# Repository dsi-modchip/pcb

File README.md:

# DSi modchip PCB and flex-cable

> [!IMPORTANT]
> ***This PCB is still a work-in-progress and has bugs.***

This repository contains the KiCAD design files for the DSi modchip and the
cable flex-PCB.

## Notes

Currently, you'll have to order and make these yourself. I don't think making
them widely available already is a good idea, there's still a few bugs left in
the design.

The issues with the modchip PCB itself are listed [here](/wifi-interposer/TODO-r2.2.).
Additionally, inserting a cable into the modchips USB socket too forcefully can
cause the modchip PCB to snap in half, which is bad.

I haven't actually gotten the flex-cable to work properly. There are problems
with either a too large parasitic capacitance on the glitch signal line, or bad
contacts between the flexPCB and the glitching MOSFET. I suggest deadbugging
the crowbar MOSFET instead, if that's something you're capable of.

## Ordering/fab instructions

The modchip is a 4-layer board that should be 0.8 mm thick. I've gotten it
fabbed successfully from both Aisler (at 1.6mm thickness) and JLCPCB.

The flex-cable consists of two layers, needs stiffner in certain places, and
has been fabbed from JLCPCB.

## Bill of Materials

### Modchip main components

These are all the components required for the core functionality of the modchip.

| Reference | Value       | Footprint | Qty | Farnell n° | LCSC n° | Mouser n° |
|:--------- |:----------- |:--------- | ---:| ----------:| -------:|:--------- |
| C3,C4     | 27pF C0G    | 0402      | 2   | 4539081    | C880615 | 603-CC402GRNPO9BN270 |
| C5,C6,C7,C10,C11,C12,C13,C14,C15,C16,C17 | 100nF | 0402 | 11 | 1758880 | C16772 | 791-0402B224K100CT |
| C8,C9     | 1uF         | 0402      | 2   | 3013332    | C12530  | 187-CL05A105KP5NNNC |
| J1        | Molex SlimStack 501920-5001 | | 1 | N/A    | N/A     | 538-501920-5001 |
| J5        | Molex 200528-0040 |     | 1   | 3500399    | N/A     | 538-200528-0040 |
| Q4        | Dual NPMOS  | SOT-363/SC-70-6|1|3828400    | C155499 | 621-DMC3400SDW-13 |
| R1,R2     | 10k         | 0402      | 2   | 2787800    | C25744  | 279-CRG0402J10K/10 |
| R5        | 47k         | 0402      | 2   | 4004532    | C25792  | 279-CRG0402J47K |
| R7,R8     | 1k          | 0402      | 2   | 4004531    | C11702  | 603-RC0402FR-131KL |
| SW1, SW2  | 1P1T button | 4.2x3.2mm | 2   | 3703693    | C2689510| 611-RKB2SJM250SMTRLF |
| U1        | RP2040      | QFN-56 P0.4 | 1 | 3766082    | C2040   | 358-SC09147 |
| U2,U4     | W25Q16JVUXIQ | DFN-8 P0.5mm |2| N/A        | C2983691| 454-W25Q16JVUXIQTR |
| Y2        | 12 MHz 18pF | SMD3225 GND2/4 | 1 | 3572992 | C7424717| 774-403C35D12M00000 |

> [!NOTE]
> `J5` is optional, and is only needed when you use the flex-cable. It can be
> omitted when deadbugging the crowbar MOSFET.

> [!TIP]
> * For Q4, several compatible components exist: Diodes DMC{2710U,3400S,3401L}DW,
>   Toshiba SSM6L35FU.
> * For SW1 and SW2, you can use one of the following:
>   * C&K {RKB,PTS81[05]}2SJ[GKM]250SMTR LF
>   * Alps Alpine SKRPABE010
>   * E-Switch TL3365AF180QG
>   * CUI TS20-42-25-WT-160-SMT-TR
>   * Wurth 434123025826 or 434133025816
> * For U1, you could try using the RP2350A **once its erratum E9 has been
>   fixed in hardware**.
> * For U2 and U4, any similarly-sized 3.3V >100MHz QSPI flash chip should work.
>   Requirements on U4 are lower (only 1-bit SPI, 16 MHz) but it's often cheaper
>   to buy the same chip in bulk.
> * For Y2, try e.g. ECS-120-18-33 or ABM8(G)-12.000MHZ-18

### Modchip optional: USB connector

> [!IMPORTANT]
> You most likely want this, though *technically* everything can be done using
> an SWD debugger instead.

| Reference | Value       | Footprint | Qty | Farnell n° | LCSC n° | Mouser n° |
|:--------- |:----------- |:--------- | ---:| ----------:| -------:|:--------- |
| C1,C2     | 1uF         | 0402      | 2   | 3013332    | C12530  | 187-CL05A105KP5NNNC |
| F1        | 0.5A        | 0603      | 1   | 2850001    | C163116 | 530-C2Q500 |
| J3        | USBC 2.0 Recp | USBC 16P| 1   | 3819289    | C428463 | 640-USB4520031A |
| R3,R11    | 47k         | 0402      | 2   | 4004532    | C25792  | 279-CRG0402J47K |
| R6,R12    | 5.1k        | 0402      | 2   | 2447201    | C25905  | 708-RMCF0402FT5K10 |
| R9,R10    | 27 1%       | 0402      | 2   | 4014781    | C100623 | 791-RMC1/16SK27R0FTH |
| U6        | AP2127K-3.3 | SOT-23-5  | 1   | 2510377    | C81233  | 998-MIC5504-3.3YM5TR |
| U3        | D1213A-02SM | SOT-23-5  | 1   | 3946109    | N/A     | 621-D1213A-02SM-7 |
| U7        | USBLC6-2SC6 | SOT-23-6  | 1   | 1269406    | C2827654| 511-USBLC6-2SC6 |

> [!IMPORTANT]
> Use only one of `U3` or `U7`, never both!

### Modchip optional: LED

It indicates the status, except it doesn't work because there's no proper 5V
rail available when plugged into the DSi.

| Reference | Value       | Footprint | Qty | Farnell n° | LCSC n° | Mouser n° |
|:--------- |:----------- |:--------- | ---:| ----------:| -------:|:--------- |
| D1        | WS2812B     | PLCC-2020 | 1   | N/A        | C965555 | 485-4684  |
| R13       | 330         | 0402      | 1   | TODO       | TODO    | TODO      |

### Modchip optional: WiFi module carrier

With a few extra components, you can make the modchip act as a real interposer
PCB between the DSi motherboard and the WiFi module.

| Reference | Value       | Footprint | Qty | Farnell n° | LCSC n° | Mouser n° |
|:--------- |:----------- |:--------- | ---:| ----------:| -------:|:--------- |
| C18,C19   | 1uF         | 0402      | 2   | 3013332    | C12530  | 187-CL05A105KP5NNNC |
| J2        | Molex SlimStack 52991-0508 | | 1 | 3500613 | N/A     | 538-52991-0508 |
| U5        | MIC5317-1.8YD5 | SOT-23-5 | 1 | 2809977    | C236669 | 998-MIC5504-1.8YM5TR |

> [!NOTE]
> Only short `JP1` if you intend to talk to the WiFi module in a standalone
> (i.e. non-interposer) manner.

> [!TIP]
> Instead of a MIC5317, many other SOT-23-5 LDOs such as the MIC5504-1.8YM5 can
> be used instead. I tend to pick ones with a low quiescent current. **Do pay
> attention to the pinout, though, as it sometimes changes even between
> SOT-23-5 parts of the same vendor.**

### Modchip optional: I2C level shifter

This can be a neat extra if you want to talk to the DSi's I2C bus. This was
used during modchip development, but isn't required at runtime.

| Reference | Value       | Footprint | Qty | Farnell n° | LCSC n° | Mouser n° |
|:--------- |:----------- |:--------- | ---:| ----------:| -------:|:--------- |
| C21       | 100nF       | 0402      | 1   | 1758880    | C16772  | 791-0402B224K100CT |
| R4        | 200k        | 0402      | 1   | 3537789    | C25764  | 791-WR04X2003FTL |
| U8        | PCA9306DC1  | VSSOP-8   | 1   | 2400482    | C33196  | 595-PCA9306DCUR |

> [!TIP]
> Instead of a PCA9306 (from either TI or NXP), an LSF0102 (from TI or
> Nexperia) or Nexperia NCA9306 can be used as well.

### Flex-cable

The flex-cable only needs a single IRFHS8342PbF as crowbar MOSFET. There's also
a footprint for a small 0402 series resistance at the gate (e.g. 200 Ohm), but
it can be shorted.

## Installing the modchip, flashing firmware and payload

See [the guide](https://github.com/dsi-modchip/guide?tab=readme-ov-file#dsi-modchip-guide).

## License

[CERN OHL-S v2](/LICENSE)

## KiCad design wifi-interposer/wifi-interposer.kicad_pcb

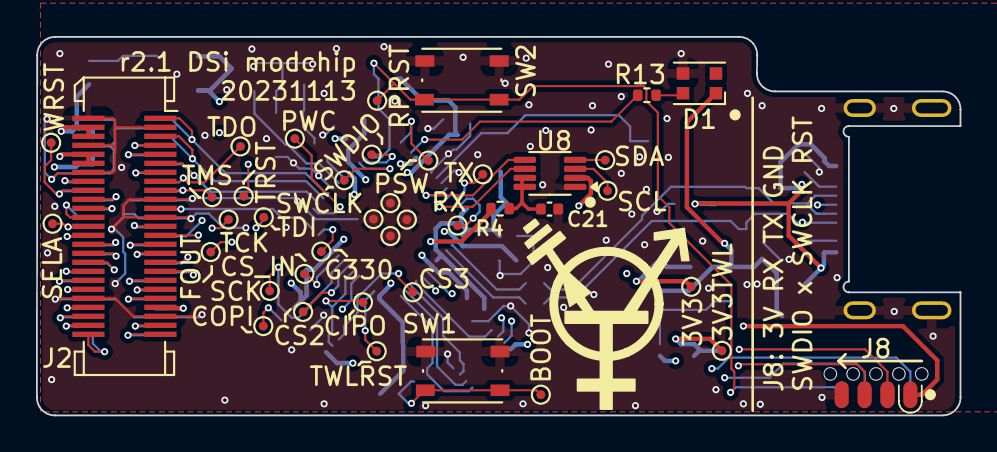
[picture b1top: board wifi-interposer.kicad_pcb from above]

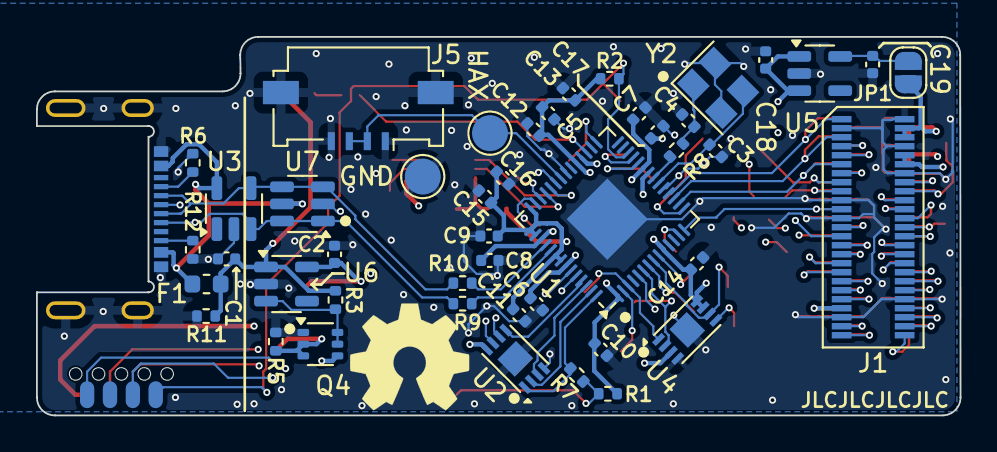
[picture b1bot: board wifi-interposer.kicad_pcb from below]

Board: 4 copper layers, 51.3 x 21.0 mm, 87 parts (46 on the bottom side), 81 nets.

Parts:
C1, C2, C8, C9, C18, C19: 1uF; C_0402_1005Metric
C3, C4: 27pF; C_0402_1005Metric
C5, C6, C7, C10, C11, C12, C13, C14, C15, C16, C17, C21: 100nF; C_0402_1005Metric
D1: WS2812B; LED_WS2812B-2020_PLCC4_2.0x2.0mm
F1: 0.5A; Fuse_0603_1608Metric
J1: TWL_WifiConn_Plug_TO_MAINBRD; Molex_SlimStack_501920-5001_2x25_P0.50mm_Vertical
J2: TWL_WifiConn_Rcpt_TO_WIFIBRD; Molex_SlimStack_52991-0508_2x25_P0.50mm_Vertical
J3: USB_C_Receptacle_USB2.0; USB_C_Receptacle_GCT_USB4510
J5: GlitchFPC; Molex_200528-0040_1x04-1MP_P1.00mm_Horizontal
J8: SOICbite; SOIC_clipProgSmall
JP1: SolderJumper_2_Open; SolderJumper-2_P1.3mm_Open_RoundedPad1.0x1.5mm
Q4: Q_Dual_NPMOS_S1G1D2S2G2D1; SOT-363_SC-70-6
R1, R2: 10k; R_0402_1005Metric
R3, R5, R11: 47k; R_0402_1005Metric
R4: 200k; R_0402_1005Metric
R6, R12: 5.1k; R_0402_1005Metric
R7, R8: 1k; R_0402_1005Metric
R9, R10: 27 1%; R_0402_1005Metric
R13: 330; R_0402_1005Metric
SW1, SW2: SW_Push; SW_Push_1P1T_NO_Vertical_Wuerth_434133025816
TP1: To glitch FET; TestPoint_Pad_D2.0mm
TP2: GND2 on CPU-TWL-01 PCB, TP14 on CPU-UTL-01 PCB; TestPoint_Pad_D2.0mm
TP3: SCK; TestPoint_Circular_D0.5
TP4: COPI; TestPoint_Circular_D0.5
TP5: CIPO; TestPoint_Circular_D0.5
TP6: CS_IN; TestPoint_Circular_D0.5
TP7: CS2; TestPoint_Circular_D0.5
TP8: CS3; TestPoint_Circular_D0.5
TP9: TDO; TestPoint_Circular_D0.5
TP10: TMS; TestPoint_Circular_D0.5
TP11: TDI; TestPoint_Circular_D0.5
TP12: TCK; TestPoint_Circular_D0.5
TP13: TRST; TestPoint_Circular_D0.5
TP14: FOUT; TestPoint_Circular_D0.5
TP15: SELA; TestPoint_Circular_D0.5
TP16: WRST; TestPoint_Circular_D0.5
TP17: TWLRST; TestPoint_Circular_D0.5
TP18: 3V3TWL; TestPoint_Circular_D0.5
TP19: 3V3; TestPoint_Circular_D0.5
TP20: RPRST; TestPoint_Circular_D0.5
TP21: BOOT; TestPoint_Circular_D0.5
TP22: TX; TestPoint_Circular_D0.5
TP23: RX; TestPoint_Circular_D0.5
TP24: SWCLK; TestPoint_Circular_D0.5
TP25: SWDIO; TestPoint_Circular_D0.5
TP29: SCL; TestPoint_Circular_D0.5
TP30: SDA; TestPoint_Circular_D0.5
TP32: G330; TestPoint_Circular_D0.5
TP33: PWC; TestPoint_Circular_D0.5
TP34, TP35, TP36, TP37: GND; TestPoint_Circular_D0.5
TP38: PSW; TestPoint_Circular_D0.5
U1: RP2040; QFN-56-1EP_7x7mm_P0.4mm_EP3.2x3.2mm
U2, U4: W25Q16JVUXIQ; DFN-8-1EP_3x2mm_P0.5mm_EP1.36x1.46mm
U3: D1213A-02SM; SOT-23-5
U5: MIC5317-1.8YD5; SOT-23-5
U6: AP2127K-3.3; SOT-23-5
U7: USBLC6-2SC6; SOT-23-6
U8: PCA9306DC1; VSSOP-8_2.3x2mm_P0.5mm
Y2: 12.000MHz; Crystal_SMD_3225-4Pin_3.2x2.5mm

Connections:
1V8_MBRD: J1.4 (VDD18), J1.6 (VDD18), J2.4 (VDD18), J2.6 (VDD18), JP1.2 (B), U8.2 (VREF1)
3V3_MBRD: J1.10 (VDD33), J1.12 (VDD33), Q4.2 (G), Q4.3 (D), R5.1, TP18.1, U1.32 (GPIO21)
+1V1: C6.2, C7.2, C8.2, U1.23 (DVDD), U1.45 (VREG_VOUT), U1.50 (DVDD)
+3V3: C2.1, C5.1, C9.1, C10.1, C11.1, C12.1, C13.1, C14.1, C15.1, C16.1, C17.2, C18.1, J2.10 (VDD33), J2.12 (VDD33), J8.1, Q4.4 (S), R1.1, R2.1, R4.2, TP19.1, U1.1 (IOVDD), U1.10 (IOVDD), U1.22 (IOVDD), U1.33 (IOVDD), U1.42 (IOVDD), U1.43 (ADC_AVDD), U1.44 (VREG_IN), U1.48 (USB_VDD), U1.49 (IOVDD), U2.8 (VCC), U4.3 (IO2), U4.7 (IO3), U4.8 (VCC), U5.1 (VIN), U5.3 (EN), U6.5 (VOUT)
+5V: F1.1, J3.A4 (VBUS), J3.A9 (VBUS), J3.B4 (VBUS), J3.B9 (VBUS), U3.5, U7.5 (VBUS)
/D+: R9.1, U1.47 (USB_DP)
/D-: R10.2, U1.46 (USB_DM)
/LED_WS2812: R13.2, U1.31 (GPIO20)
/QSPI_CLK: U1.52 (QSPI_SCLK), U2.6 (CLK)
/QSPI_SD0: U1.53 (QSPI_SD0), U2.5 (DI(IO0))
/QSPI_SD1: U1.55 (QSPI_SD1), U2.2 (DO(IO1))
/QSPI_SD2: U1.54 (QSPI_SD2), U2.3 (IO2)
/QSPI_SD3: U1.51 (QSPI_SD3), U2.7 (IO3)
/QSPI_~CS: R7.2, U1.56 (QSPI_SS), U2.1 (~CS)
/SCL33: U1.39 (GPIO27_ADC1), U8.6 (SCL2)
/SDA33: U1.38 (GPIO26_ADC0), U8.5 (SDA2)
/USB_D+: J3.A6 (D+), J3.B6 (D+), R9.2, U3.3, U7.1 (I/O1), U7.6 (I/O1)
/USB_D-: J3.A7 (D-), J3.B7 (D-), R10.1, U3.4, U7.3 (I/O2), U7.4 (I/O2)
/XIN: C3.2, U1.20 (XIN), Y2.3
/XOUT: C4.2, R8.1, Y2.1
/power/CC1: J3.A5 (CC1), R6.1
/power/CC2: J3.B5 (CC2), R12.1
/power/EN: Q4.5 (G), Q4.6 (D), R3.2, U6.3 (EN)
ATH_TX_H: J1.16 (ATH_TX_H), J2.16 (ATH_TX_H)
BBP_SCS: J1.35 (BBP_SCS), J2.35 (BBP_SCS)
BBP_SLEEP: J1.29 (BBP_SLEEP), J2.29 (BBP_SLEEP)
BB_RF_SCLK: J1.41 (BB_RF_SCLK), J2.41 (BB_RF_SCLK)
BB_RF_SDI: J1.39 (BB_RF_SDI), J2.39 (BB_RF_SDI)
BB_RF_SDO: J1.37 (BB_RF_SDO), J2.37 (BB_RF_SDO)
BTN_~BOOT: R1.2, R7.1, SW1.1, TP21.1
BTN_~RESET: J8.5, R2.2, SW2.1, TP20.1, U1.26 (RUN)
CCA: J1.36 (CCA), J2.36 (CCA)
FLASH_~WP: J1.28 (FLASH_~WP), J2.28 (FLASH_~WP)
GLITCH_OUT: J5.2, J5.3, TP1.1, U1.36 (GPIO24)
GND: C1.2, C2.2, C3.1, C4.1, C5.2, C6.1, C7.1, C8.1, C9.2, C10.2, C11.2, C12.2, C13.2, C14.2, C15.2, C16.2, C17.1, C18.2, C19.2, C21.2, D1.3 (VSS), J1.2 (GND), J1.3 (GND), J1.8 (GND), J1.14 (GND), J1.19 (GND), J1.23 (GND), J1.42 (GND), J1.45 (GND), J2.2 (GND), J2.3 (GND), J2.8 (GND), J2.14 (GND), J2.19 (GND), J2.23 (GND), J2.42 (GND), J2.45 (GND), J3.A1 (GND), J3.A12 (GND), J3.B1 (GND), J3.B12 (GND), J3.S1 (SHIELD), J5.1, J5.4, J5.MP (MountPin), J8.4, Q4.1 (S), R5.2, R6.2, R11.2, R12.2, SW1.2, SW2.2, TP2.1, TP34.1, TP35.1, TP36.1, TP37.1, U1.19 (TESTEN), U1.35 (GPIO23), U1.37 (GPIO25), U1.57 (GND), U2.4 (GND), U2.9 (EP), U3.2, U4.4 (GND), U4.9 (EP), U5.2 (GND), U6.2 (GND), U7.2 (GND), U8.1 (GND), Y2.2, Y2.4
GPIO330: TP32.1, U1.13 (GPIO10)
I2C_SCL: TP29.1, U8.3 (SCL1)
I2C_SDA: TP30.1, U8.4 (SDA1)
JTAG_TCK: J1.22 (JTAG_TCK), J2.22 (JTAG_TCK), TP12.1
JTAG_TDI: J1.20 (JTAG_TDI), J2.20 (JTAG_TDI), TP11.1
JTAG_TDO: J1.15 (JTAG_TDO), J2.15 (JTAG_TDO), TP9.1
JTAG_TMS: J1.17 (JTAG_TMS), J2.17 (JTAG_TMS), TP10.1
JTAG_~TRST: J1.24 (JTAG_~TRST), J2.24 (JTAG_~TRST), TP13.1
MCLK: J1.47 (MCLK), J2.47 (MCLK)
NC: J1.25 (NC), J2.25 (NC)
unnamed: D1.4 (DIN), R13.1
unnamed: C19.1, JP1.1 (A), U5.5 (VOUT)
unnamed: R8.2, U1.21 (XOUT)
unnamed: C21.1, R4.1, U8.7 (VREF2), U8.8 (EN)
P49: J1.49, J2.49
POWERCUT: TP33.1, U1.15 (GPIO12)
PWSW: TP38.1, U1.29 (GPIO18)
RESET: J1.50 (RESET), J2.50 (RESET), TP17.1, U1.2 (GPIO0)
RF_SCS: J1.33 (RF_SCS), J2.33 (RF_SCS)
RF_SLEEP: J1.31 (RF_SLEEP), J2.31 (RF_SLEEP)
RTC_FOUT: J1.21 (RTC_FOUT), J2.21 (RTC_FOUT), TP14.1, U1.14 (GPIO11)
SDIO_CLK: J1.1 (SDIO_CLK), J2.1 (SDIO_CLK), U1.18 (GPIO15)
SDIO_CMD: J1.11 (SDIO_CMD), J2.11 (SDIO_CMD), U1.16 (GPIO13)
SDIO_DAT0: J1.5 (SDIO_DAT0), J2.5 (SDIO_DAT0), U1.17 (GPIO14)
SDIO_DAT1: J1.9 (SDIO_DAT1), J2.9 (SDIO_DAT1)
SDIO_DAT2: J1.13 (SDIO_DAT2), J2.13 (SDIO_DAT2)
SDIO_DAT3: J1.7 (SDIO_DAT3), J2.7 (SDIO_DAT3)
SPI_CIPO: J1.32 (SPI_CIPO), J2.32 (SPI_CIPO), TP5.1, U1.6 (GPIO4), U4.2 (DO(IO1))
SPI_CLK: J1.30 (SPI_SCK), J2.30 (SPI_SCK), TP3.1, U1.8 (GPIO6), U4.6 (CLK)
SPI_COPI: J1.34 (SPI_COPI), J2.34 (SPI_COPI), TP4.1, U1.5 (GPIO3), U4.5 (DI(IO0))
SPI_~CS2: J2.27 (SPI_~CS2), TP7.1, U1.7 (GPIO5)
SPI_~CS3: TP8.1, U1.3 (GPIO1), U4.1 (~CS)
SPI_~CS_IN: J1.27 (SPI_~CS2), TP6.1, U1.9 (GPIO7)
SWCLK: J8.6, TP24.1, U1.24 (SWCLK)
SWDIO: J8.8, TP25.1, U1.25 (SWD)
TRCLK: J1.44 (TRCLK), J2.44 (TRCLK)
TRDATA: J1.40 (TRDATA), J2.40 (TRDATA)
TRRDY: J1.46 (TRRDY), J2.46 (TRRDY)
UART_RX: J8.2, TP23.1, U1.41 (GPIO29_ADC3)
UART_TX: J8.3, TP22.1, U1.40 (GPIO28_ADC2)
VBUS: C1.1, D1.1 (VDD), F1.2, R3.1, R11.1, U6.1 (VIN)
VDD18?: J1.43 (VDD18?), J2.43 (VDD18?)
WL_RXPE: J1.38 (WL_RXPE), J2.38 (WL_RXPE)
WL_TXPE: J1.48 (WL_TXPE), J2.48 (WL_TXPE)
~SEL_ATH: J1.26 (~SEL_ATH), J2.26 (~SEL_ATH), TP15.1
~WIFI_RST: J1.18 (~WIFI_RST), J2.18 (~WIFI_RST), TP16.1

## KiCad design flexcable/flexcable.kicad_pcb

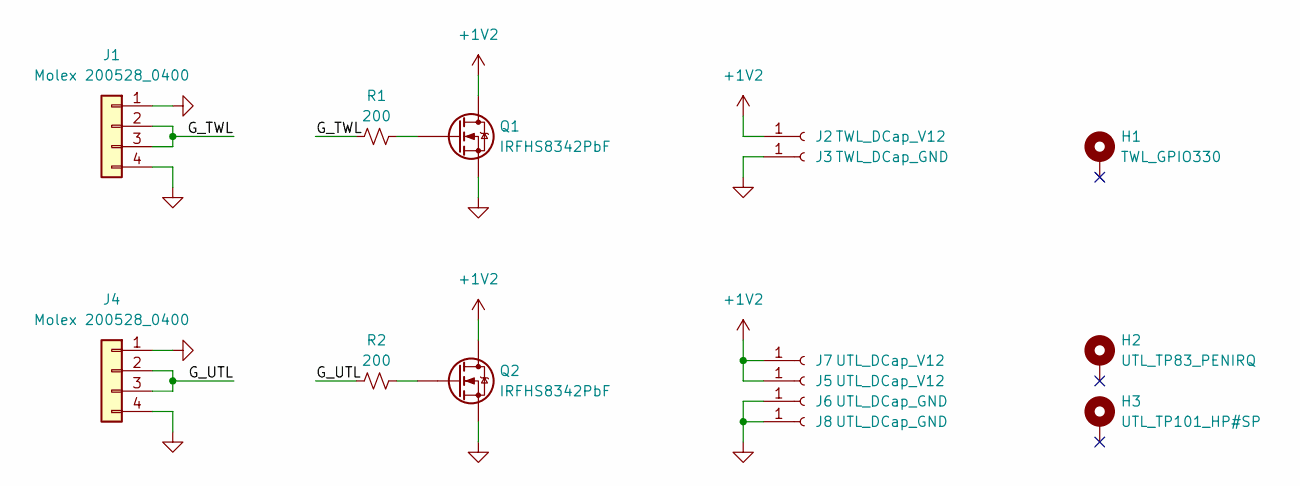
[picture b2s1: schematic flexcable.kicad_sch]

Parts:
H1: TWL_GPIO330; TestPointAnchor_D1.00
H2: UTL_TP83_PENIRQ; TestPointAnchor_D1.00
H3: UTL_TP101_HP#SP; TestPointAnchor_D1.00
J1, J4: Molex 200528_0400; Molex_2005280040_FPC
J2: TWL_DCap_V12; FPC_Castellated_Hole
J3: TWL_DCap_GND; FPC_Castellated_Hole
J5, J7: UTL_DCap_V12; FPC_Castellated_Hole
J6, J8: UTL_DCap_GND; FPC_Castellated_Hole
Q1, Q2: IRFHS8342PbF; PQFN6_2X2_INF
R1, R2: 200; R_0402_1005Metric

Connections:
+1V2: J2.1, J5.1, J7.1, Q1.1 (D), Q1.2 (D), Q1.5 (D), Q1.6 (D), Q1.7 (D), Q2.1 (D), Q2.2 (D), Q2.5 (D), Q2.6 (D), Q2.7 (D)
/G_TWL: J1.2, J1.3, R1.1
/G_UTL: J4.2, J4.3, R2.1
GND: J1.1, J1.4, J3.1, J4.1, J4.4, J6.1, J8.1, Q1.4 (S), Q1.8 (S), Q2.4 (S), Q2.8 (S)
unnamed: Q1.3 (G), R1.2
unnamed: Q2.3 (G), R2.2

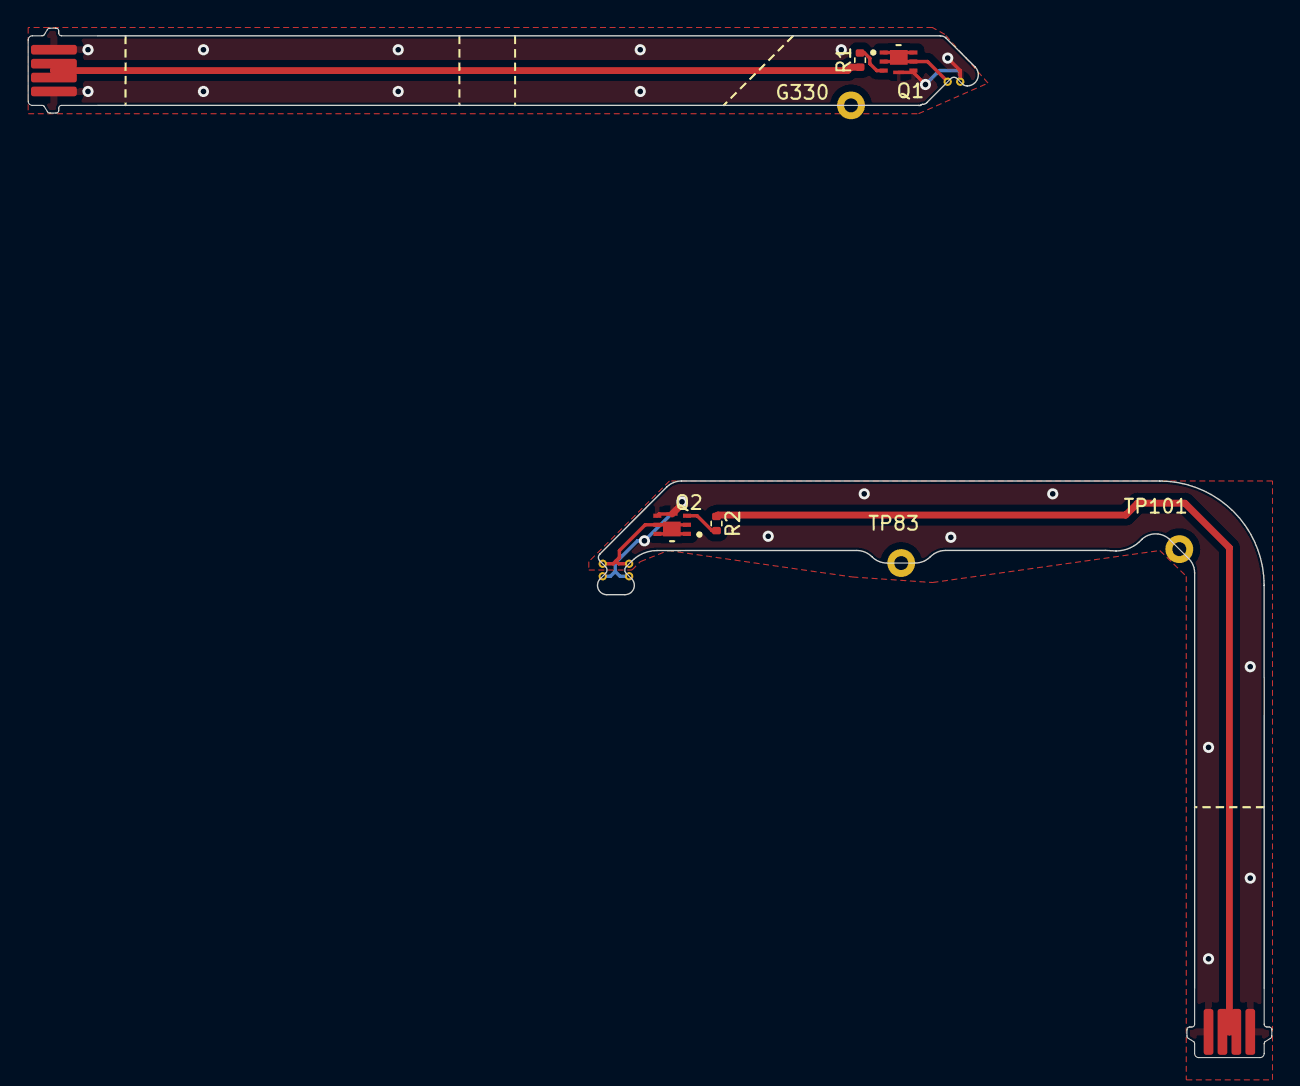
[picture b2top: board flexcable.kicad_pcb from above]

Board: 2 copper layers, 89.4 x 74.0 mm, 15 parts (0 on the bottom side), 6 nets.

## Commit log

2024-01-05 initial (flexcable only)
2024-01-05 stuff
2024-01-08 first fabable versions
2024-01-09 push so that i can work on this on a desktop
2024-01-09 WIP moving stuff around to make it fit
2024-01-10 version ready-ish for fabrication
2024-01-10 final tweaks (hopefully)
2024-09-19 add wifi-interposer pcb design
2024-09-22 add README with BOM listing
